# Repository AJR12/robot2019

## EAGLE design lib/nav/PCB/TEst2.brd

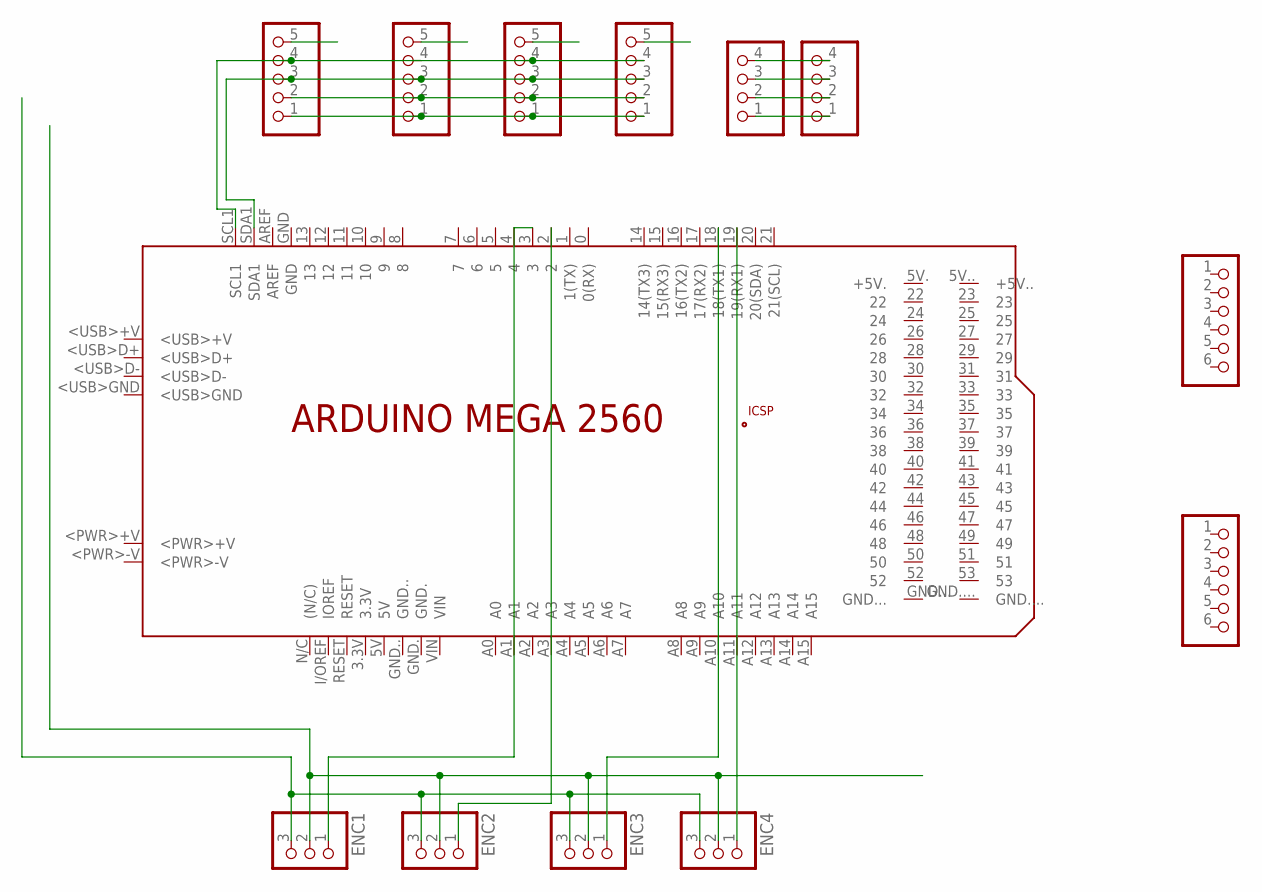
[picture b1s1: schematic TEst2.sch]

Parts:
ENC1, ENC2, ENC3, ENC4: PINHD-1X3; 1X03
IMU: PINHD-1X4; 1X04
L1, L2, L3, L4: PINHD-1X55X2MM; 1_05X2MM
MC1, MC2: PINHD-1X6; 1X06
OLED: PINHD-1X4; 1X04
PCB1: ARDUINO_MEGA2560

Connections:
unnamed: L1.3, L2.3, L3.3, L4.3, PCB1.SDA1
unnamed: IMU.1, OLED.1
unnamed: IMU.2, OLED.2
unnamed: ENC1.1, PCB1.3
unnamed: L1.4, L2.4, L3.4, L4.4, PCB1.SCL1
unnamed: ENC2.1, PCB1.2
unnamed: ENC1.3, ENC2.3, ENC3.3, ENC4.3
unnamed: ENC1.2, ENC2.2, ENC3.2, ENC4.2
unnamed: IMU.3, OLED.3
unnamed: ENC3.1, PCB1.18 (18(TX1))
unnamed: ENC4.1, PCB1.19 (19(RX1))
unnamed: IMU.4, OLED.4
unnamed: L1.1, L2.1, L3.1, L4.1
unnamed: L1.2, L2.2, L3.2, L4.2

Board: 2 copper layers, 13 parts (1 on the bottom side), 14 nets, no tracks yet.

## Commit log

2018-08-25 new code
2018-08-25 comment
2018-08-25 new comment
2018-09-01 comit
2018-09-03 3 loops Code
2018-09-08 commiting
2018-09-08 code
2018-09-08 alright
2018-09-08 AbdulCom
2018-09-22 pid control
2019-01-04 IMU test file
2019-01-04 IMU intergrated
2019-01-05 integrated lasers, imu, and oled
2019-01-05 testing motor class
2019-01-10 comitting
2019-02-16 Latest with i2c Comm
